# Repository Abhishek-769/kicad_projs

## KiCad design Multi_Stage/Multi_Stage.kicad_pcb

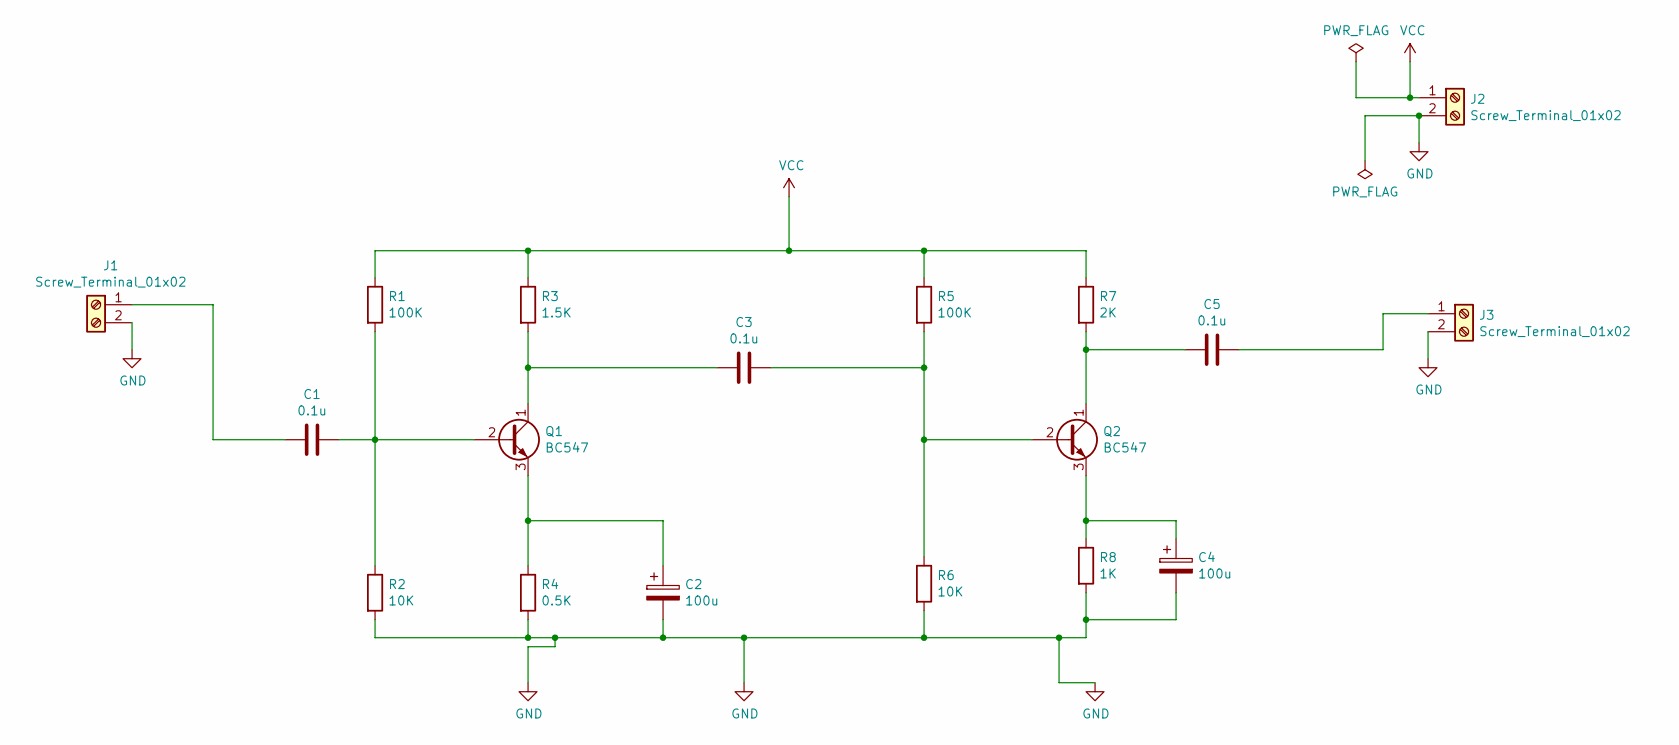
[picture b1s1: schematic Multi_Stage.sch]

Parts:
C1, C3, C5: 0.1u; C_Disc_D3.0mm_W2.0mm_P2.50mm
C2, C4: 100u; CP_Radial_D5.0mm_P2.50mm
J1, J2, J3: Screw_Terminal_01x02; TerminalBlock_Phoenix_MKDS-1,5-2_1x02_P5.00mm_Horizontal
Q1, Q2: BC547; TO-92
R1, R5: 100K; R_Axial_DIN0309_L9.0mm_D3.2mm_P12.70mm_Horizontal
R2, R6: 10K; R_Axial_DIN0309_L9.0mm_D3.2mm_P12.70mm_Horizontal
R3: 1.5K; R_Axial_DIN0309_L9.0mm_D3.2mm_P12.70mm_Horizontal
R4: 0.5K; R_Axial_DIN0309_L9.0mm_D3.2mm_P12.70mm_Horizontal
R7: 2K; R_Axial_DIN0309_L9.0mm_D3.2mm_P12.70mm_Horizontal
R8: 1K; R_Axial_DIN0309_L9.0mm_D3.2mm_P12.70mm_Horizontal

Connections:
GND: C2.2, C4.2, J1.2, J2.2, J3.2, R2.2, R4.2, R6.2, R8.2
unnamed: C1.1, Q1.2 (B), R1.2, R2.1
unnamed: C1.2, J1.1
unnamed: C2.1, Q1.3 (E), R4.1
unnamed: C3.1, Q2.2 (B), R5.2, R6.1
unnamed: C3.2, Q1.1 (C), R3.2
unnamed: C4.1, Q2.3 (E), R8.1
unnamed: C5.1, J3.1
unnamed: C5.2, Q2.1 (C), R7.2
VCC: J2.1, R1.1, R3.1, R5.1, R7.1

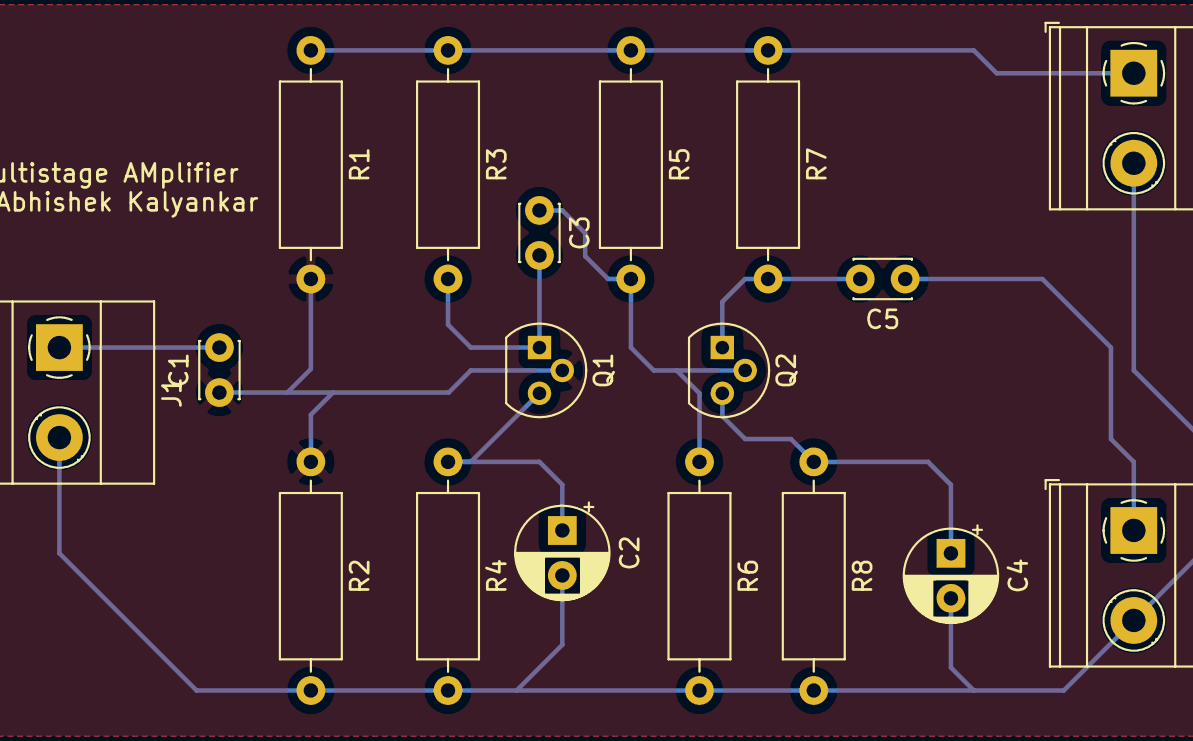
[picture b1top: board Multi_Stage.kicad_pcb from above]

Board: 2 copper layers, 18 parts (0 on the bottom side), 10 nets.

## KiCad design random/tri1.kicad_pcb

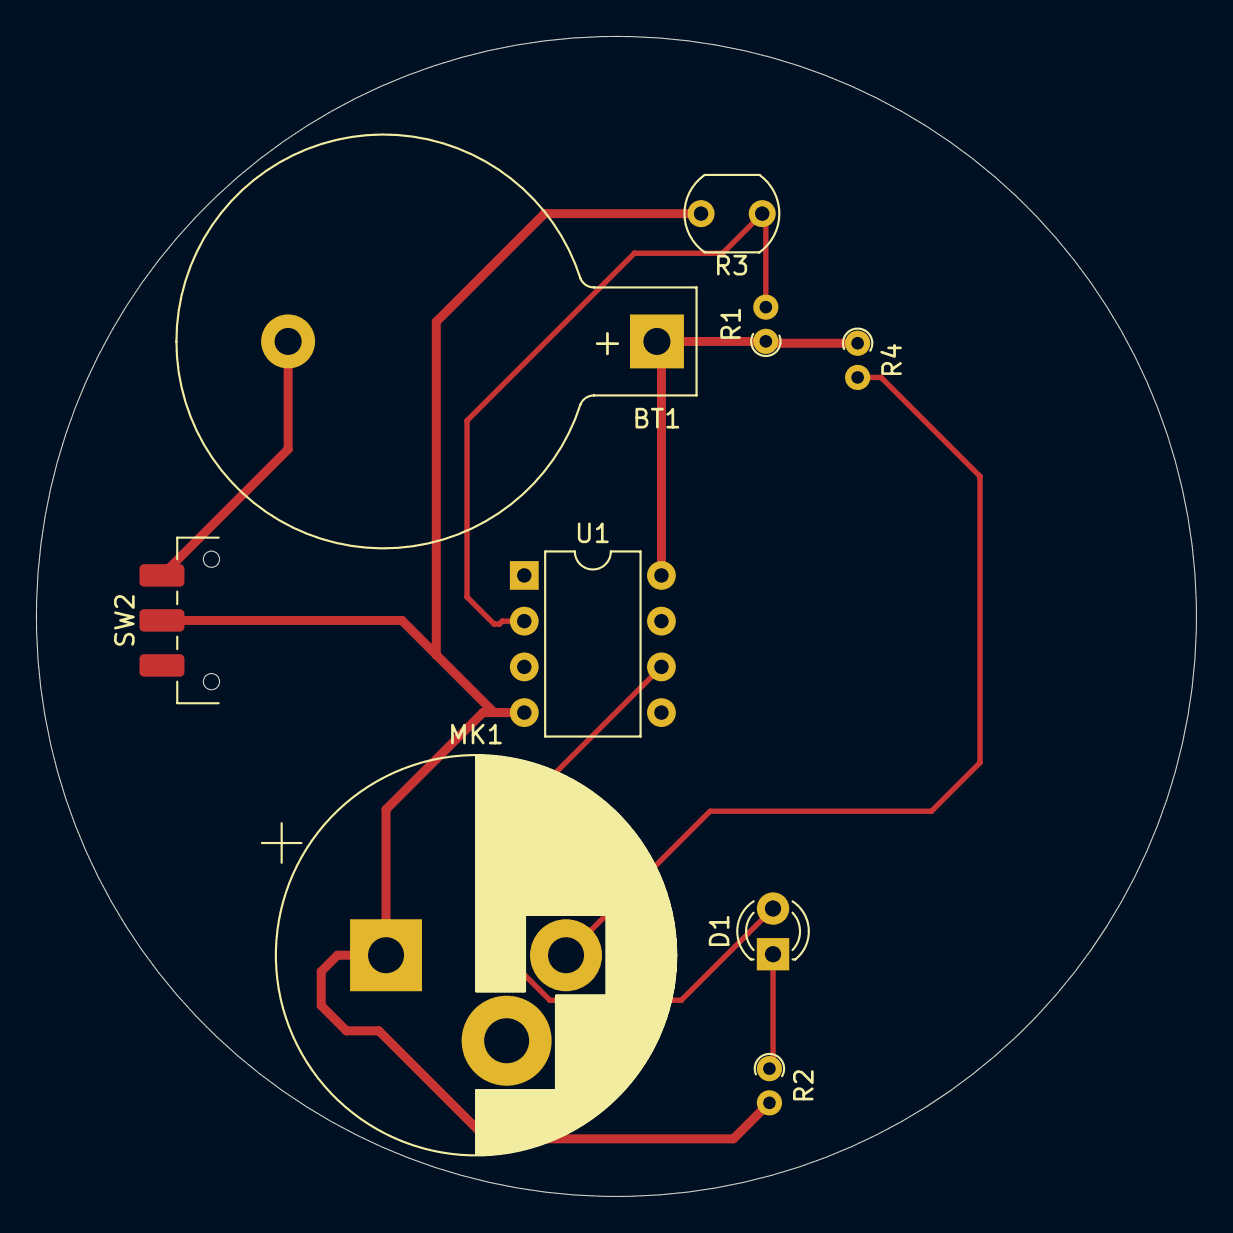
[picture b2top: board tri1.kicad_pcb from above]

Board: 2 copper layers, 64.4 x 64.4 mm, 9 parts (0 on the bottom side), 7 nets.

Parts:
BT1: Battery_Cell; BatteryHolder_Keystone_103_1x20mm
D1: LED; LED_D3.0mm
MK1: Microphone_Condenser; CP_Radial_D22.0mm_P10.00mm_3pin_SnapIn
R1: 10K; R_Axial_DIN0204_L3.6mm_D1.6mm_P1.90mm_Vertical
R2: 470; R_Axial_DIN0204_L3.6mm_D1.6mm_P1.90mm_Vertical
R3: LDR07; R_LDR_5.1x4.3mm_P3.4mm_Vertical
R4: 5.6K; R_Axial_DIN0204_L3.6mm_D1.6mm_P1.90mm_Vertical
SW2: SW_SPDT; SW_SPDT_CK_JS102011SAQN
U1: ATtiny85-20P; DIP-8_W7.62mm

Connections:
+3.3V: BT1.1 (+), R1.1, R4.1, U1.8 (VCC)
/LDR: R1.2, R3.1, U1.2 (XTAL1/PB3)
/Lawda: D1.2 (A), U1.6 (PB1)
GND: MK1.1 (-), R2.2, R3.2, SW2.2 (B), U1.4 (GND)
unnamed: BT1.2 (-), SW2.3 (C)
unnamed: D1.1 (K), R2.1
unnamed: MK1.2 (+), R4.2

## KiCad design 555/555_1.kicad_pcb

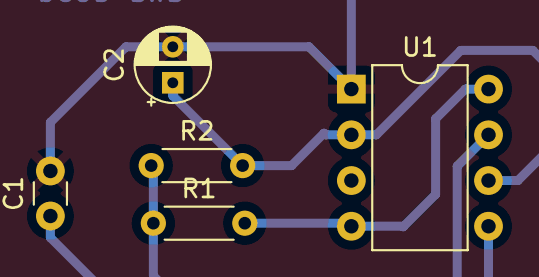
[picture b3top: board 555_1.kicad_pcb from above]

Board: 2 copper layers, 5 parts (0 on the bottom side), 5 nets.

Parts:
C1: 0.01uF; C_Disc_D3.0mm_W1.6mm_P2.50mm
C2: 0.1uF; CP_Radial_D4.0mm_P2.00mm
R1, R2: 50K; R_Axial_DIN0204_L3.6mm_D1.6mm_P5.08mm_Horizontal
U1: ICM7555xP; DIP-8_W7.62mm

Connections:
GND: C1.2, C2.2, U1.1 (GND)
unnamed: C1.1, U1.5 (CV)
unnamed: R1.1, R2.1, U1.7 (DIS)
unnamed: R1.2, U1.4 (R), U1.8 (VCC)
unnamed: C2.1, R2.2, U1.2 (TR), U1.6 (THR)

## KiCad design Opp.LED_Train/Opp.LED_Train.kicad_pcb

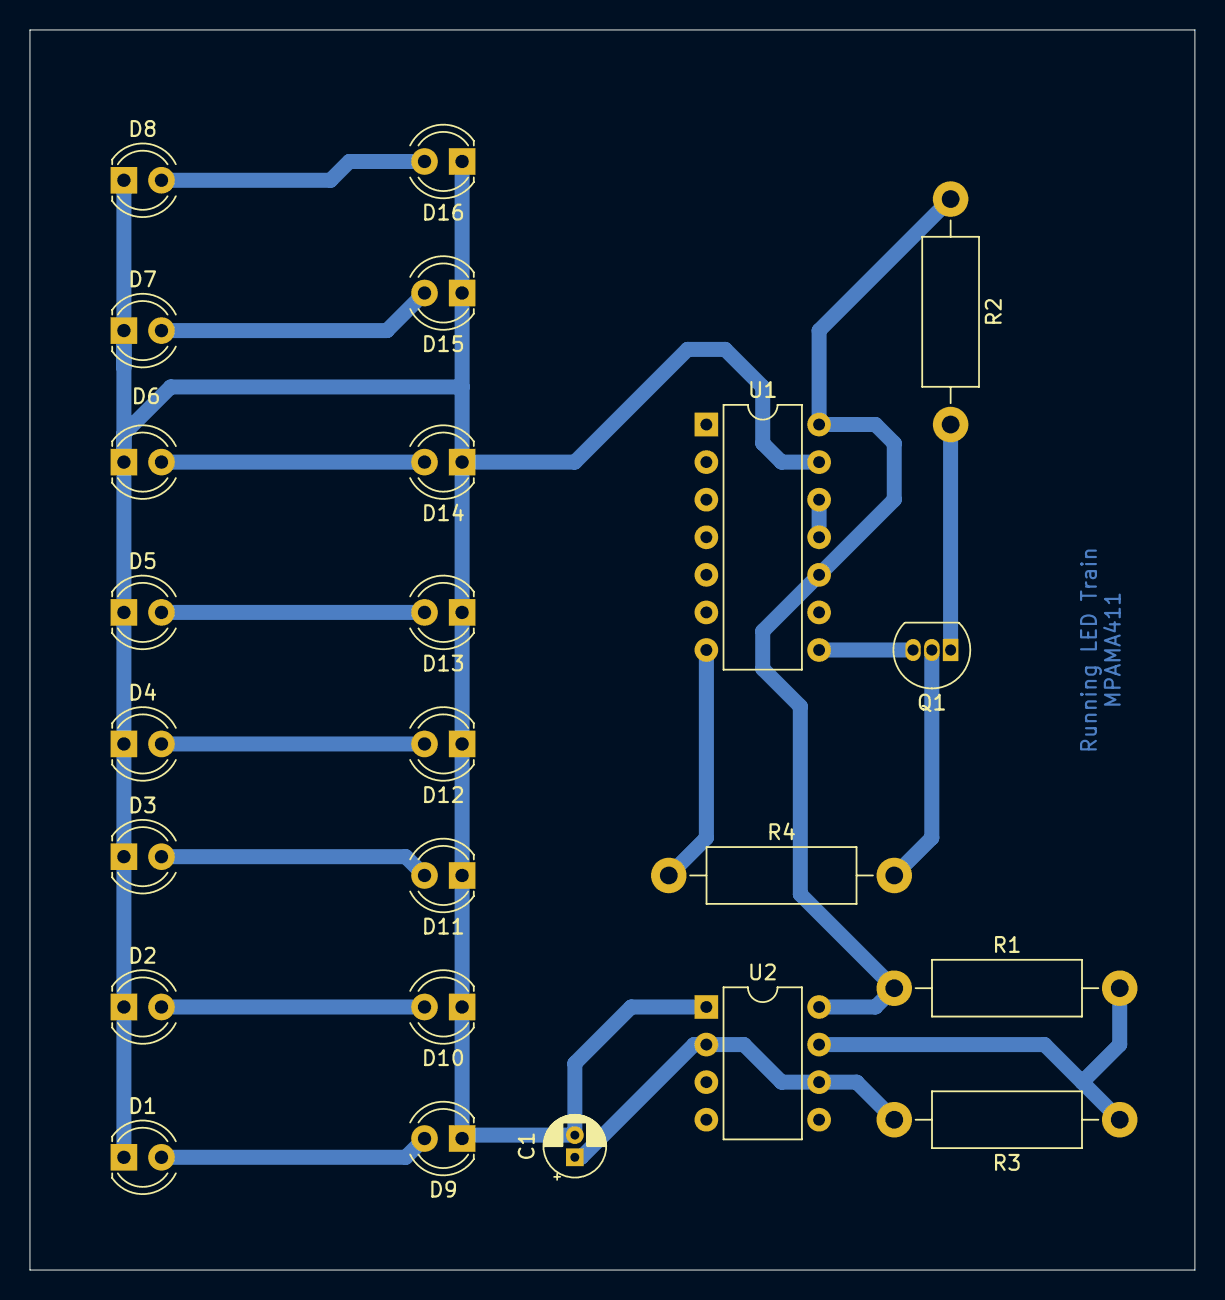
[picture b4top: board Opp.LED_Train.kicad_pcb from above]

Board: 2 copper layers, 78.7 x 83.8 mm, 24 parts (0 on the bottom side), 16 nets.

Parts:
C1: 10uF; CP_Radial_D4.0mm_P1.50mm
D1, D2, D3, D4, D5, D6, D7, D8, D9, D10, D11, D12, D13, D14, D15, D16: LED; LED_D4.0mm
Q1: BC547; TO-92_Inline
R1, R3: 4.7K; R_Axial_DIN0411_L9.9mm_D3.6mm_P15.24mm_Horizontal
R2, R4: 6.8K; R_Axial_DIN0411_L9.9mm_D3.6mm_P15.24mm_Horizontal
U1: 74HC595; DIP-14_W7.62mm
U2: NE555P; DIP-8_W7.62mm

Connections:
unnamed: C1.1, R3.2, U2.2, U2.6
unnamed: C1.2, D1.1, D2.1, D3.1, D4.1, D5.1, D6.1, D7.1, D8.1, D9.1, D10.1, D11.1, D12.1, D13.1, D14.1, D15.1, D16.1, U1.13, U2.1
unnamed: D1.2, D9.2, R4.1, U1.7
unnamed: D2.2, D10.2, U1.6
unnamed: D3.2, D11.2, U1.5
unnamed: D4.2, D12.2, U1.4
unnamed: D5.2, D13.2, U1.3
unnamed: D6.2, D14.2, U1.2
unnamed: D7.2, D15.2, U1.1
unnamed: D8.2, D16.2
unnamed: Q1.1, R2.2
unnamed: Q1.2, R4.2
unnamed: Q1.3, U1.8
unnamed: R1.1, R2.1, U1.10, U1.14, U2.8
unnamed: R1.2, R3.1, U2.7
unnamed: U1.11, U1.12, U2.3

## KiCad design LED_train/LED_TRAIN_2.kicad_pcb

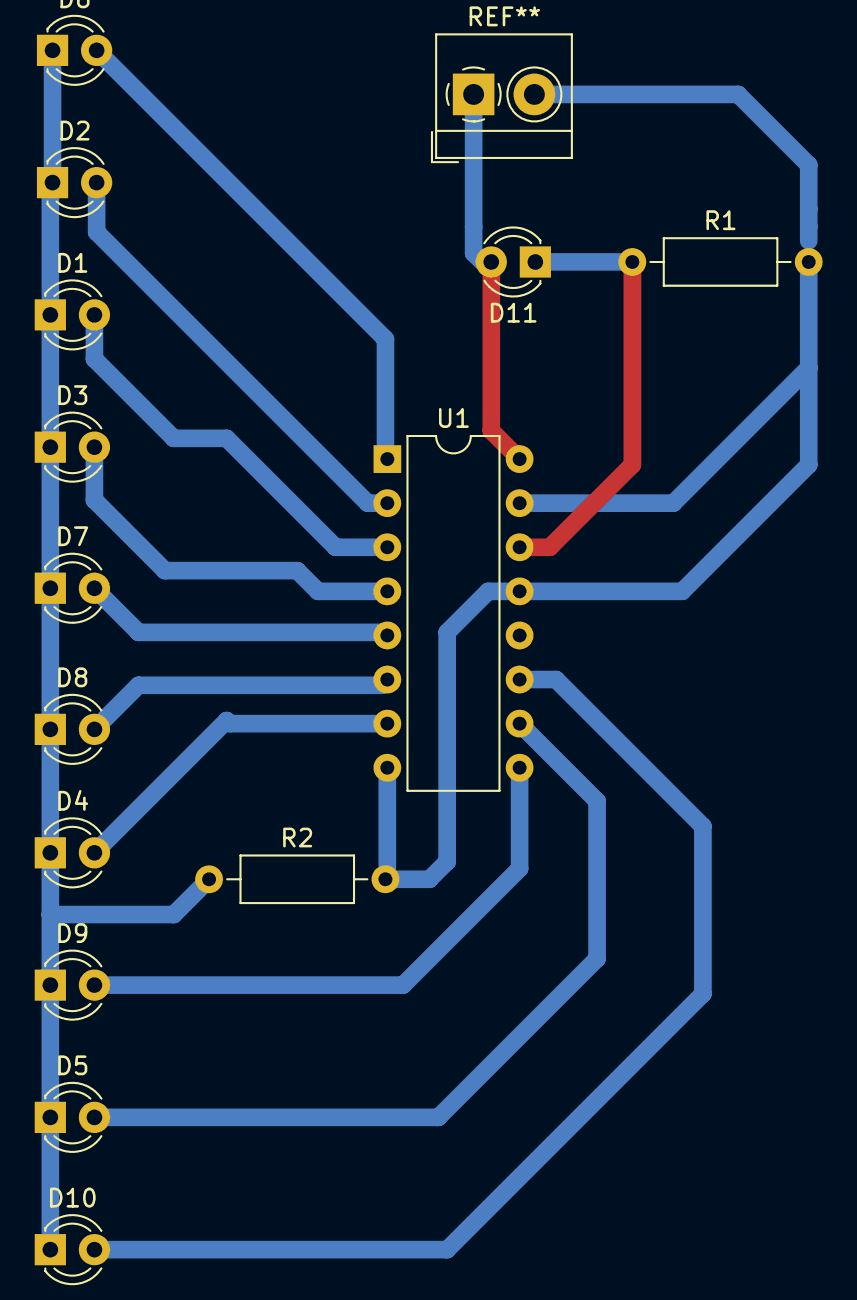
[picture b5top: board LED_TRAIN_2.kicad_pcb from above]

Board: 2 copper layers, 14 parts (0 on the bottom side), 14 nets.

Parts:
D1, D2, D3, D4, D5, D6, D7, D8, D9, D10, D11: LED; LED_D3.0mm
R1, R2: 470; R_Axial_DIN0207_L6.3mm_D2.5mm_P10.16mm_Horizontal
U1: 4017; DIP-16_W7.62mm

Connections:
GND: R1.2, R2.2, U1.8, U1.13, U1.15
unnamed: D1.1, D2.1, D3.1, D4.1, D5.1, D6.1, D7.1, D8.1, D9.1, D10.1, R2.1
unnamed: D1.2, U1.3
unnamed: D2.2, U1.2
unnamed: D3.2, U1.4
unnamed: D4.2, U1.7
unnamed: D5.2, U1.10
unnamed: D6.2, U1.1
unnamed: D7.2, U1.5
unnamed: D8.2, U1.6
unnamed: D9.2, U1.9
unnamed: D10.2, U1.11
unnamed: D11.1, R1.1, U1.14
VCC: D11.2, U1.16
